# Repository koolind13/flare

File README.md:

# flare
keyboard

## resources:

switches:

https://www.ipopularshop.com/products/ttc-frozen-silent-v2-linear-mechanical-switches?variant=41905974345878

(stabilizers):

https://www.microcenter.com/product/663979/Keyboard_Stabilizer_GSV2_Kit_for_Mechanical_Keyboards?storeID=081

keycaps:

https://womierkeyboard.com/products/ice-cube-clear-keycaps-crystal-ice-keycaps-set-for-mechanical-keyboard?variant=42857564143687

https://maxkeyboard.com/clear-translucent-cherry-mx-blank-keycap-set-for-esc-w-a-s-d-or-e-s-d-f-and-arrow-keys.html

screen:

https://www.waveshare.com/0.96inch-rgb-oled-module.htm

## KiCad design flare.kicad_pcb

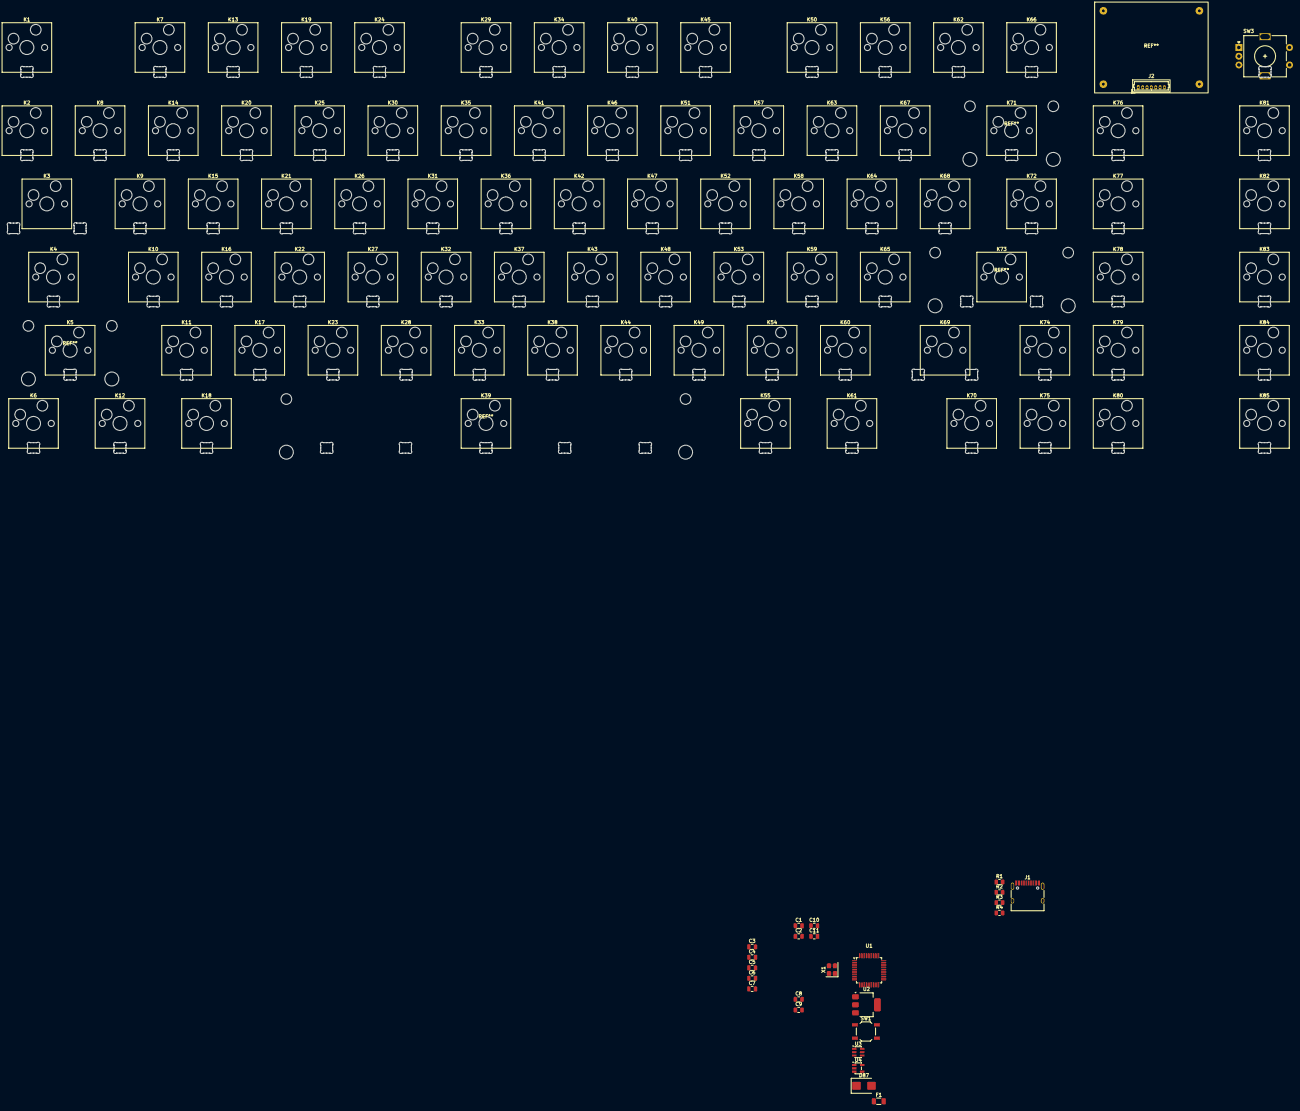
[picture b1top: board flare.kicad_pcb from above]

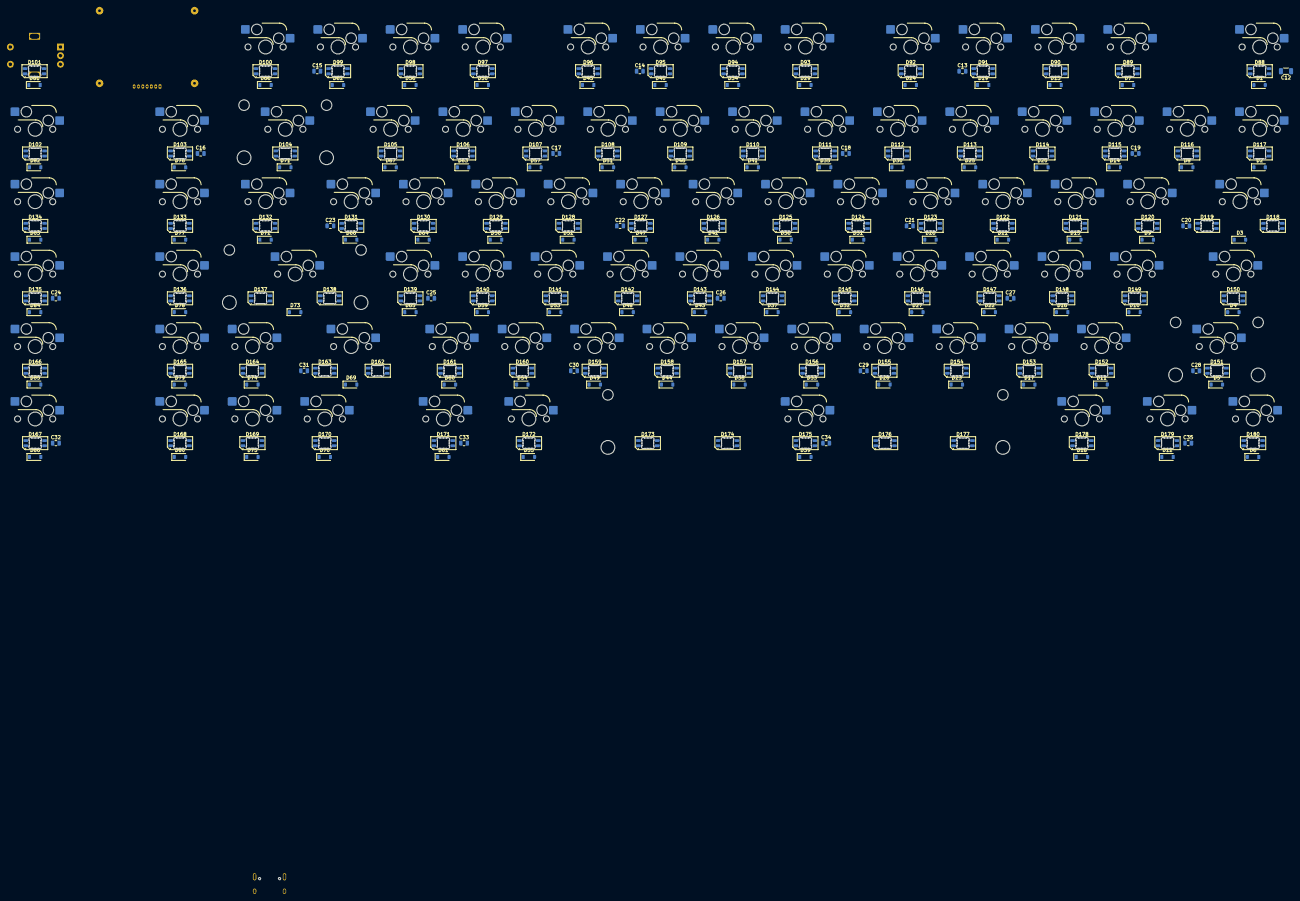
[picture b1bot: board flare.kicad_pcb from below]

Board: 2 copper layers, 314 parts (203 on the bottom side), 222 nets, no tracks yet.

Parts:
C1, C2: 22p; C_0805_2012Metric
C3: 0.1u; C_0805_2012Metric
C4, C5, C6, C7: 0.1; C_0805_2012Metric
C8, C9: 100; C_0805_2012Metric
C10, C11: 10; C_0805_2012Metric
C12: 100 µF; C_1206_3216Metric
C13, C14, C15, C16, C17, C18, C19, C20, C21, C22, C23, C24, C25, C26, C27, C28, C29, C30, C31, C32, C33, C34, C35: 0.1 µF; C_0805_2012Metric
D1, D2, D3, D4, D5, D6, D7, D8, D9, D10, D11, D12, D13, D14, D15, D16, D17, D18, D19, D20, D21, D22, D23, D24, D25, D26, D27, D28, D29, D30, D31, D32, D33, D34, D35, D36, D37, D38, D39, D40, D41, D42, D43, D44, D45, D46, D47, D48, D49, D50, D51, D52, D53, D54, D55, D56, D57, D58, D59, D60, D61, D62, D63, D64, D65, D66, D67, D68, D69, D70, D71, D72, D73, D74, D75, D76, D77, D78, D79, D80, D81, D82, D83, D84, D85, D86: D; D_SOD-123
D87: SMBJ5.0A; D_SMB
D88, D89, D90, D91, D92, D93, D94, D95, D96, D97, D98, D99, D100, D101, D102, D103, D104, D105, D106, D107, D108, D109, D110, D111, D112, D113, D114, D115, D116, D117, D118, D119, D120, D121, D122, D123, D124, D125, D126, D127, D128, D129, D130, D131, D132, D133, D134, D135, D136, D137, D138, D139, D140, D141, D142, D143, D144, D145, D146, D147, D148, D149, D150, D151, D152, D153, D154, D155, D156, D157, D158, D159, D160, D161, D162, D163, D164, D165, D166, D167, D168, D169, D170, D171, D172, D173, D174, D175, D176, D177, D178, D179, D180: SK6812MINI-E; LED_SK6812MINI-E_3.2x2.8mm_P1.5mm_ReverseMount
F1: 1.5A; Fuse_1206_3216Metric
J1: USB_C_Receptacle_USB2.0_16P; USB_C_Receptacle_HRO_TYPE-C-31-M-12
J2: OLED; Molex_PicoBlade_53047-0710_1x07_P1.25mm_Vertical
K1, K2, K3, K4, K5, K6, K7, K8, K9, K10, K11, K12, K13, K14, K15, K16, K17, K18, K19, K20, K21, K22, K23, K24, K25, K26, K27, K28, K29, K30, K31, K32, K33, K34, K35, K36, K37, K38, K39, K40, K41, K42, K43, K44, K45, K46, K47, K48, K49, K50, K51, K52, K53, K54, K55, K56, K57, K58, K59, K60, K61, K62, K63, K64, K65, K66, K67, K68, K69, K70, K71, K72, K73, K74, K75, K76, K77, K78, K79, K80, K81, K82, K83, K84, K85: KEYSW; SW_Hotswap_Kailh_MX_1.00u
R1, R2: 10k; R_0805_2012Metric
R3, R4: 5.1k; R_0805_2012Metric
SW1: SW_Push; SW_SPST_TL3342
SW3: RotaryEncoder_Switch; RotaryEncoder_Alps_EC11E-Switch_Vertical_H20mm
U1: STM32F072CBTx1; LQFP-48_7x7mm_P0.5mm
U2: AMS1117-3.3; SOT-223-3_TabPin2
U3: USBLC6-2SC6; SOT-23-6
U4: 74AHCT1G125; SOT-23-5
X1: XTAL_GND; Crystal_SMD_3225-4Pin_3.2x2.5mm

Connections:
+5V: C11.1, C12.1, C13.1, C14.1, C15.1, C16.1, C17.1, C18.1, C19.1, C20.1, C21.1, C22.1, C23.1, C24.1, C25.1, C26.1, C27.1, C28.1, C29.1, C30.1, C31.1, C32.1, C33.1, C34.1, C35.1, D87.2 (A2), D88.3 (VDD), D89.3 (VDD), D90.3 (VDD), D91.3 (VDD), D92.3 (VDD), D93.3 (VDD), D94.3 (VDD), D95.3 (VDD), D96.3 (VDD), D97.3 (VDD), D98.3 (VDD), D99.3 (VDD), D100.3 (VDD), D101.3 (VDD), D102.3 (VDD), D103.3 (VDD), D104.3 (VDD), D105.3 (VDD), D106.3 (VDD), D107.3 (VDD), D108.3 (VDD), D109.3 (VDD), D110.3 (VDD), D111.3 (VDD), D112.3 (VDD), D113.3 (VDD), D114.3 (VDD), D115.3 (VDD), D116.3 (VDD), D117.3 (VDD), D118.3 (VDD), D119.3 (VDD), D120.3 (VDD), D121.3 (VDD), D122.3 (VDD), D123.3 (VDD), D124.3 (VDD), D125.3 (VDD), D126.3 (VDD), D127.3 (VDD), D128.3 (VDD), D129.3 (VDD), D130.3 (VDD), D131.3 (VDD), D132.3 (VDD), D133.3 (VDD), D134.3 (VDD), D135.3 (VDD), D136.3 (VDD), D137.3 (VDD), D138.3 (VDD), D139.3 (VDD), D140.3 (VDD), D141.3 (VDD), D142.3 (VDD), D143.3 (VDD), D144.3 (VDD), D145.3 (VDD), D146.3 (VDD), D147.3 (VDD), D148.3 (VDD), D149.3 (VDD), D150.3 (VDD), D151.3 (VDD), D152.3 (VDD), D153.3 (VDD), D154.3 (VDD), D155.3 (VDD), D156.3 (VDD), D157.3 (VDD), D158.3 (VDD), D159.3 (VDD), D160.3 (VDD), D161.3 (VDD), D162.3 (VDD), D163.3 (VDD), D164.3 (VDD), D165.3 (VDD), D166.3 (VDD), D167.3 (VDD), D168.3 (VDD), D169.3 (VDD), D170.3 (VDD), D171.3 (VDD), D172.3 (VDD), D173.3 (VDD), D174.3 (VDD), D175.3 (VDD), D176.3 (VDD), D177.3 (VDD), D178.3 (VDD), D179.3 (VDD), D180.3 (VDD), F1.1, U2.3 (VI), U3.5 (VBUS), U4.5 (VCC)
/COL0: K1.1, K2.1, K3.1, K4.1, K5.1, K6.1, U1.10 (PA0)
/COL1: K7.1, K8.1, K9.1, K10.1, K11.1, K12.1, U1.11 (PA1)
/COL2: K13.1, K14.1, K15.1, K16.1, K17.1, K18.1, U1.12 (PA2)
/COL3: K19.1, K20.1, K21.1, K22.1, K23.1, U1.13 (PA3)
/COL4: K24.1, K25.1, K26.1, K27.1, K28.1, U1.46 (PB9)
/COL5: K29.1, K30.1, K31.1, K32.1, K33.1, U1.45 (PB8)
/COL6: K34.1, K35.1, K36.1, K37.1, K38.1, K39.1, U1.16 (PA6)
/COL7: K40.1, K41.1, K42.1, K43.1, K44.1, U1.41 (PB5)
/COL8: K45.1, K46.1, K47.1, K48.1, K49.1, U1.26 (PB13)
/COL9: K50.1, K51.1, K52.1, K53.1, K54.1, K55.1, U1.27 (PB14)
/COL10: K56.1, K57.1, K58.1, K59.1, K60.1, K61.1, U1.28 (PB15)
/COL11: K62.1, K63.1, K64.1, K65.1, U1.2 (PC13)
/COL12: K66.1, K67.1, K68.1, K69.1, K70.1, U1.3 (PC14)
/COL13: K71.1, K72.1, K73.1, K74.1, K75.1, U1.4 (PC15)
/COL14: K76.1, K77.1, K78.1, K79.1, K80.1, U1.29 (PA8)
/COL15: K81.1, K82.1, K83.1, K84.1, K85.1, SW3.S2, U1.30 (PA9)
/ENC_A: SW3.A, U1.39 (PB3)
/ENC_B: SW3.B, U1.40 (PB4)
/OLED_CS: J2.5, U1.14 (PA4)
/OLED_DC: J2.6, U1.42 (PB6)
/OLED_MOSI: J2.3, U1.17 (PA7)
/OLED_RST: J2.7, U1.43 (PB7)
/OLED_SCK: J2.4, U1.15 (PA5)
/RGB_DATA: U1.31 (PA10), U4.2
/ROW0: D1.1 (K), D7.1 (K), D13.1 (K), D19.1 (K), D24.1 (K), D29.1 (K), D34.1 (K), D40.1 (K), D45.1 (K), D50.1 (K), D56.1 (K), D62.1 (K), D66.1 (K), D81.1 (K), U1.18 (PB0)
/ROW1: D2.1 (K), D8.1 (K), D14.1 (K), D20.1 (K), D25.1 (K), D30.1 (K), D35.1 (K), D41.1 (K), D46.1 (K), D51.1 (K), D57.1 (K), D63.1 (K), D67.1 (K), D69.1 (K), D76.1 (K), D82.1 (K), U1.19 (PB1)
/ROW2: D3.1 (K), D9.1 (K), D15.1 (K), D21.1 (K), D26.1 (K), D31.1 (K), D36.1 (K), D42.1 (K), D47.1 (K), D52.1 (K), D58.1 (K), D64.1 (K), D68.1 (K), D72.1 (K), D77.1 (K), D83.1 (K), U1.20 (PB2)
/ROW3: D4.1 (K), D10.1 (K), D16.1 (K), D22.1 (K), D27.1 (K), D32.1 (K), D37.1 (K), D43.1 (K), D48.1 (K), D53.1 (K), D59.1 (K), D65.1 (K), D73.1 (K), D78.1 (K), D84.1 (K), U1.21 (PB10)
/ROW4: D5.1 (K), D11.1 (K), D17.1 (K), D23.1 (K), D28.1 (K), D33.1 (K), D38.1 (K), D44.1 (K), D49.1 (K), D54.1 (K), D60.1 (K), D70.1 (K), D74.1 (K), D79.1 (K), D85.1 (K), U1.22 (PB11)
/ROW5: D6.1 (K), D12.1 (K), D18.1 (K), D39.1 (K), D55.1 (K), D61.1 (K), D71.1 (K), D75.1 (K), D80.1 (K), D86.1 (K), U1.25 (PB12)
GND: C1.2, C2.2, C3.2, C4.2, C5.2, C6.2, C7.2, C8.2, C9.2, C10.2, C11.2, C12.2, C13.2, C14.2, C15.2, C16.2, C17.2, C18.2, C19.2, C20.2, C21.2, C22.2, C23.2, C24.2, C25.2, C26.2, C27.2, C28.2, C29.2, C30.2, C31.2, C32.2, C33.2, C34.2, C35.2, D87.1 (A1), D88.1 (VSS), D89.1 (VSS), D90.1 (VSS), D91.1 (VSS), D92.1 (VSS), D93.1 (VSS), D94.1 (VSS), D95.1 (VSS), D96.1 (VSS), D97.1 (VSS), D98.1 (VSS), D99.1 (VSS), D100.1 (VSS), D101.1 (VSS), D102.1 (VSS), D103.1 (VSS), D104.1 (VSS), D105.1 (VSS), D106.1 (VSS), D107.1 (VSS), D108.1 (VSS), D109.1 (VSS), D110.1 (VSS), D111.1 (VSS), D112.1 (VSS), D113.1 (VSS), D114.1 (VSS), D115.1 (VSS), D116.1 (VSS), D117.1 (VSS), D118.1 (VSS), D119.1 (VSS), D120.1 (VSS), D121.1 (VSS), D122.1 (VSS), D123.1 (VSS), D124.1 (VSS), D125.1 (VSS), D126.1 (VSS), D127.1 (VSS), D128.1 (VSS), D129.1 (VSS), D130.1 (VSS), D131.1 (VSS), D132.1 (VSS), D133.1 (VSS), D134.1 (VSS), D135.1 (VSS), D136.1 (VSS), D137.1 (VSS), D138.1 (VSS), D139.1 (VSS), D140.1 (VSS), D141.1 (VSS), D142.1 (VSS), D143.1 (VSS), D144.1 (VSS), D145.1 (VSS), D146.1 (VSS), D147.1 (VSS), D148.1 (VSS), D149.1 (VSS), D150.1 (VSS), D151.1 (VSS), D152.1 (VSS), D153.1 (VSS), D154.1 (VSS), D155.1 (VSS), D156.1 (VSS), D157.1 (VSS), D158.1 (VSS), D159.1 (VSS), D160.1 (VSS), D161.1 (VSS), D162.1 (VSS), D163.1 (VSS), D164.1 (VSS), D165.1 (VSS), D166.1 (VSS), D167.1 (VSS), D168.1 (VSS), D169.1 (VSS), D170.1 (VSS), D171.1 (VSS), D172.1 (VSS), D173.1 (VSS), D174.1 (VSS), D175.1 (VSS), D176.1 (VSS), D177.1 (VSS), D178.1 (VSS), D179.1 (VSS), D180.1 (VSS), J1.A1 (GND), J1.A12 (GND), J1.B1 (GND), J1.B12 (GND), J1.SH (SHIELD), J2.2, R2.1, R3.1, R4.1, SW1.1, SW3.C, U1.8 (VSSA), U1.23 (VSS), U1.35 (VSS), U1.47 (VSS), U2.1 (GND), U3.2 (GND), U4.1, U4.3 (GND), X1.3
unnamed: D1.2 (A), K1.2
unnamed: D2.2 (A), K2.2
unnamed: D3.2 (A), K3.2
unnamed: D4.2 (A), K4.2
unnamed: D5.2 (A), K5.2
unnamed: D6.2 (A), K6.2
unnamed: D7.2 (A), K7.2
unnamed: D8.2 (A), K8.2
unnamed: D9.2 (A), K9.2
unnamed: D10.2 (A), K10.2
unnamed: D11.2 (A), K11.2
unnamed: D12.2 (A), K12.2
unnamed: D13.2 (A), K13.2
unnamed: D14.2 (A), K14.2
unnamed: D15.2 (A), K15.2
unnamed: D16.2 (A), K16.2
unnamed: D17.2 (A), K17.2
unnamed: D18.2 (A), K18.2
unnamed: D19.2 (A), K19.2
unnamed: D20.2 (A), K20.2
unnamed: D21.2 (A), K21.2
unnamed: D22.2 (A), K22.2
unnamed: D23.2 (A), K23.2
unnamed: D24.2 (A), K24.2
unnamed: D25.2 (A), K25.2
unnamed: D26.2 (A), K26.2
unnamed: D27.2 (A), K27.2
unnamed: D28.2 (A), K28.2
unnamed: D29.2 (A), K29.2
unnamed: D30.2 (A), K30.2
unnamed: D31.2 (A), K31.2
unnamed: D32.2 (A), K32.2
unnamed: D33.2 (A), K33.2
unnamed: D34.2 (A), K34.2
unnamed: D35.2 (A), K35.2
unnamed: D36.2 (A), K36.2
unnamed: D37.2 (A), K37.2
unnamed: D38.2 (A), K38.2
unnamed: D39.2 (A), K39.2
unnamed: D40.2 (A), K40.2
unnamed: D41.2 (A), K41.2
unnamed: D42.2 (A), K42.2
unnamed: D43.2 (A), K43.2
unnamed: D44.2 (A), K44.2
unnamed: D45.2 (A), K45.2
unnamed: D46.2 (A), K46.2
unnamed: D47.2 (A), K47.2
unnamed: D48.2 (A), K48.2
unnamed: D49.2 (A), K49.2
unnamed: D50.2 (A), K50.2
unnamed: D51.2 (A), K51.2
unnamed: D52.2 (A), K52.2
unnamed: D53.2 (A), K53.2
unnamed: D54.2 (A), K54.2
unnamed: D55.2 (A), K55.2
unnamed: D56.2 (A), K56.2
unnamed: D57.2 (A), K57.2
unnamed: D58.2 (A), K58.2
unnamed: D59.2 (A), K59.2
unnamed: D60.2 (A), K60.2
unnamed: D61.2 (A), K61.2
unnamed: D62.2 (A), K62.2
unnamed: D63.2 (A), K63.2
unnamed: D64.2 (A), K64.2
unnamed: D65.2 (A), K65.2
unnamed: D66.2 (A), K66.2
unnamed: D67.2 (A), K67.2
unnamed: D68.2 (A), K68.2
unnamed: D69.2 (A), K71.2
unnamed: D70.2 (A), K69.2
unnamed: D71.2 (A), K70.2
unnamed: D72.2 (A), K72.2
unnamed: D73.2 (A), K73.2
unnamed: D74.2 (A), K74.2
unnamed: D75.2 (A), K75.2
unnamed: D76.2 (A), K76.2
unnamed: D77.2 (A), K77.2
unnamed: D78.2 (A), K78.2
unnamed: D79.2 (A), K79.2
unnamed: D80.2 (A), K80.2
unnamed: D81.2 (A), SW3.S1
unnamed: D82.2 (A), K81.2
unnamed: D83.2 (A), K82.2
unnamed: D84.2 (A), K83.2
unnamed: D85.2 (A), K84.2
unnamed: D86.2 (A), K85.2
unnamed: D88.2 (DIN), U4.4
unnamed: D88.4 (DOUT), D89.2 (DIN)
unnamed: D89.4 (DOUT), D90.2 (DIN)
unnamed: D90.4 (DOUT), D91.2 (DIN)
unnamed: D91.4 (DOUT), D92.2 (DIN)
unnamed: D92.4 (DOUT), D93.2 (DIN)
unnamed: D93.4 (DOUT), D94.2 (DIN)
unnamed: D94.4 (DOUT), D95.2 (DIN)
unnamed: D95.4 (DOUT), D96.2 (DIN)
unnamed: D96.4 (DOUT), D97.2 (DIN)
unnamed: D97.4 (DOUT), D98.2 (DIN)
unnamed: D98.4 (DOUT), D99.2 (DIN)
unnamed: D99.4 (DOUT), D100.2 (DIN)
unnamed: D100.4 (DOUT), D101.2 (DIN)
unnamed: D101.4 (DOUT), D102.2 (DIN)
unnamed: D102.4 (DOUT), D103.2 (DIN)
unnamed: D103.4 (DOUT), D104.2 (DIN)
unnamed: D104.4 (DOUT), D105.2 (DIN)
unnamed: D105.4 (DOUT), D106.2 (DIN)
unnamed: D106.4 (DOUT), D107.2 (DIN)
unnamed: D107.4 (DOUT), D108.2 (DIN)
unnamed: D108.4 (DOUT), D109.2 (DIN)
unnamed: D109.4 (DOUT), D110.2 (DIN)
unnamed: D110.4 (DOUT), D111.2 (DIN)
unnamed: D111.4 (DOUT), D112.2 (DIN)
unnamed: D112.4 (DOUT), D113.2 (DIN)
unnamed: D113.4 (DOUT), D114.2 (DIN)
unnamed: D114.4 (DOUT), D115.2 (DIN)
unnamed: D115.4 (DOUT), D116.2 (DIN)
unnamed: D116.4 (DOUT), D117.2 (DIN)
unnamed: D117.4 (DOUT), D118.2 (DIN)
unnamed: D118.4 (DOUT), D119.2 (DIN)
unnamed: D119.4 (DOUT), D120.2 (DIN)
unnamed: D120.4 (DOUT), D121.2 (DIN)
unnamed: D121.4 (DOUT), D122.2 (DIN)
unnamed: D122.4 (DOUT), D123.2 (DIN)
unnamed: D123.4 (DOUT), D124.2 (DIN)
unnamed: D124.4 (DOUT), D125.2 (DIN)
unnamed: D125.4 (DOUT), D126.2 (DIN)
unnamed: D126.4 (DOUT), D127.2 (DIN)
unnamed: D127.4 (DOUT), D128.2 (DIN)
unnamed: D128.4 (DOUT), D129.2 (DIN)
unnamed: D129.4 (DOUT), D130.2 (DIN)
unnamed: D130.4 (DOUT), D131.2 (DIN)
unnamed: D131.4 (DOUT), D132.2 (DIN)
unnamed: D132.4 (DOUT), D133.2 (DIN)
unnamed: D133.4 (DOUT), D134.2 (DIN)
unnamed: D134.4 (DOUT), D135.2 (DIN)
unnamed: D135.4 (DOUT), D136.2 (DIN)
unnamed: D136.4 (DOUT), D137.2 (DIN)
unnamed: D137.4 (DOUT), D138.2 (DIN)
unnamed: D138.4 (DOUT), D139.2 (DIN)
unnamed: D139.4 (DOUT), D140.2 (DIN)
unnamed: D140.4 (DOUT), D141.2 (DIN)
unnamed: D141.4 (DOUT), D142.2 (DIN)
unnamed: D142.4 (DOUT), D143.2 (DIN)
unnamed: D143.4 (DOUT), D144.2 (DIN)
unnamed: D144.4 (DOUT), D145.2 (DIN)
unnamed: D145.4 (DOUT), D146.2 (DIN)
unnamed: D146.4 (DOUT), D147.2 (DIN)
unnamed: D147.4 (DOUT), D148.2 (DIN)
unnamed: D148.4 (DOUT), D149.2 (DIN)
unnamed: D149.4 (DOUT), D150.2 (DIN)
unnamed: D150.4 (DOUT), D151.2 (DIN)
unnamed: D151.4 (DOUT), D152.2 (DIN)
unnamed: D152.4 (DOUT), D153.2 (DIN)
unnamed: D153.4 (DOUT), D154.2 (DIN)
unnamed: D154.4 (DOUT), D155.2 (DIN)
unnamed: D155.4 (DOUT), D156.2 (DIN)
unnamed: D156.4 (DOUT), D157.2 (DIN)
unnamed: D157.4 (DOUT), D158.2 (DIN)
unnamed: D158.4 (DOUT), D159.2 (DIN)
unnamed: D159.4 (DOUT), D160.2 (DIN)
unnamed: D160.4 (DOUT), D161.2 (DIN)
unnamed: D161.4 (DOUT), D162.2 (DIN)
unnamed: D162.4 (DOUT), D163.2 (DIN)
unnamed: D163.4 (DOUT), D164.2 (DIN)
unnamed: D164.4 (DOUT), D165.2 (DIN)
unnamed: D165.4 (DOUT), D166.2 (DIN)
unnamed: D166.4 (DOUT), D180.2 (DIN)
unnamed: D179.2 (DIN), D180.4 (DOUT)
unnamed: D178.2 (DIN), D179.4 (DOUT)
unnamed: D177.2 (DIN), D178.4 (DOUT)
unnamed: D176.2 (DIN), D177.4 (DOUT)
unnamed: D175.2 (DIN), D176.4 (DOUT)
unnamed: D174.2 (DIN), D175.4 (DOUT)
unnamed: D173.2 (DIN), D174.4 (DOUT)
unnamed: D172.2 (DIN), D173.4 (DOUT)
unnamed: D171.2 (DIN), D172.4 (DOUT)
unnamed: D169.2 (DIN), D170.4 (DOUT)
unnamed: D168.2 (DIN), D169.4 (DOUT)
unnamed: D167.2 (DIN), D168.4 (DOUT)
unnamed: F1.2, J1.A4 (VBUS), J1.A9 (VBUS), J1.B4 (VBUS), J1.B9 (VBUS)
unnamed: J1.A5 (CC1), R4.2
unnamed: J1.B5 (CC2), R3.2
unnamed: J1.A6 (D+), J1.B6 (D+), U3.4 (I/O2)
unnamed: J1.A7 (D-), J1.B7 (D-), U3.6 (I/O1)
unnamed: R2.2, U1.44 (BOOT0)
unnamed: C8.1, R1.2, SW1.2, U1.7 (NRST)
unnamed: U1.32 (PA11), U3.1 (I/O1)
unnamed: U1.33 (PA12), U3.3 (I/O2)
unnamed: C2.1, U1.5 (PF0), X1.2
unnamed: C1.1, U1.6 (PF1), X1.1
VCC: C3.1, C4.1, C5.1, C6.1, C7.1, C9.1, C10.1, R1.1, U1.1 (VBAT), U1.9 (VDDA), U1.24 (VDD), U1.36 (VDDIO2), U1.48 (VDD), U2.2 (VO)
